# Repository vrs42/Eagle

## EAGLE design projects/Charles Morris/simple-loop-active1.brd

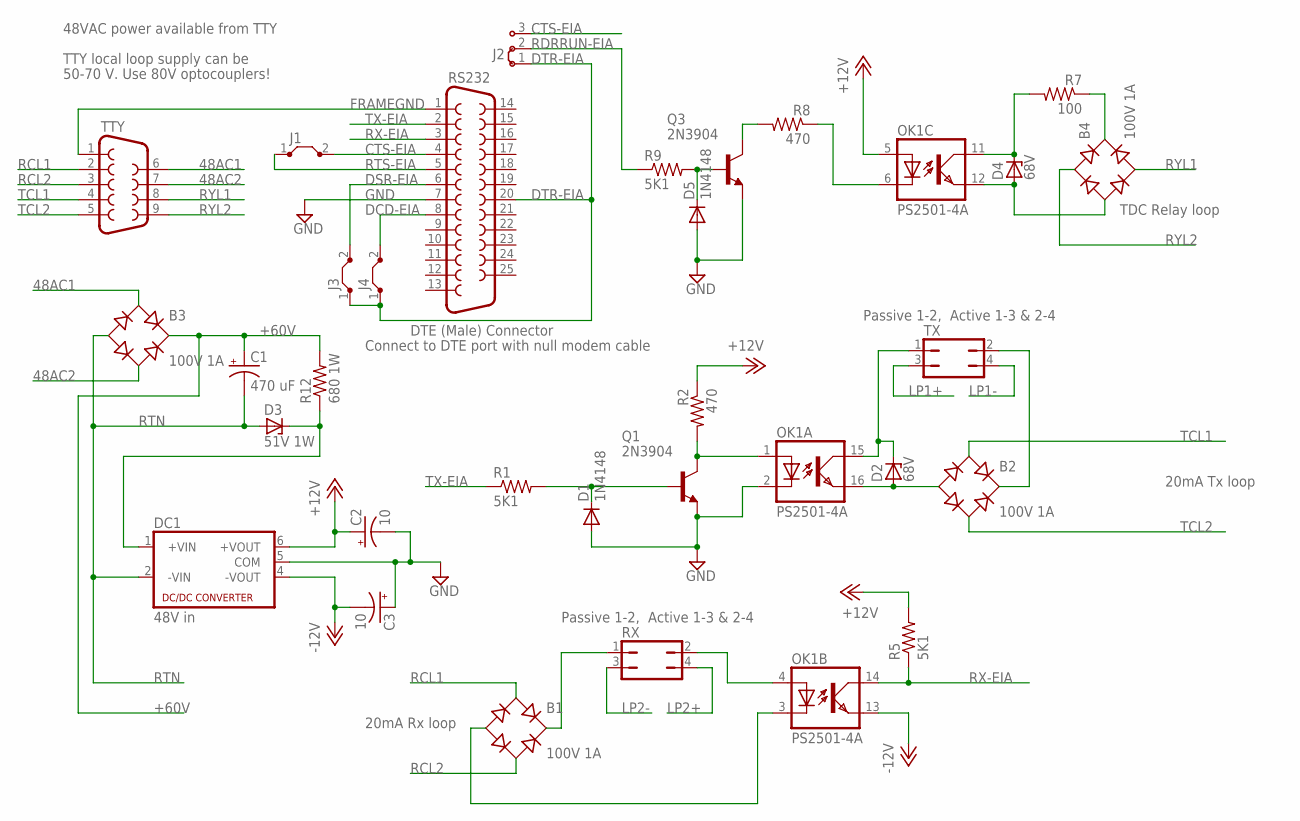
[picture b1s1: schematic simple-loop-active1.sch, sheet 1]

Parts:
B1, B2, B3, B4: 100V 1A; RB1A
C1: 470 uF; E7,5-18
C2, C3: 10; B45181A
D1, D5: 1N4148; DO35-10
D2, D4: 68V; DO41Z10
D3: 51V 1W; DO41Z10
DC1: 48V in; NMA
J1, J3, J4: J5MM; 05
J2: J2X5MM; 05C
OK1: PS2501-4A; DIL16
Q1, Q3: 2N3904; TO92
R1, R5, R9: 5K1; 0207/10
R2, R8: 470; 0207/10
R7: 100; 0207/10
R12: 680 1W; P0817V
RS232: F25H
RX: JP2Q
TTY: F09H
TX: JP2Q

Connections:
48AC1: B3.AC1, TTY.6
48AC2: B3.AC2, TTY.7
+12V: C2.+, DC1.6 (+VOUT), OK1.5 (A), R2.1, R5.2
+48VDC: D3.C, DC1.1 (+VIN), R12.1
+60V: B3.+, C1.+, R12.2; also elsewhere on the board
-12V: C3.-, DC1.4 (-VOUT), OK1.13 (EMIT)
CTS-EIA: J1.2, J2.3, RS232.4
DCD-EIA: J4.2, RS232.8
DSR-EIA: J3.2, RS232.6
DTR-EIA: J2.1, J3.1, J4.1, RS232.20
FRAMEGND: RS232.1, TTY.1
GND: C2.-, C3.+, D1.A, D5.A, DC1.5 (COM), OK1.2 (C), Q1.3 (E), Q3.3 (E), RS232.7
LP1+: TX.3; also elsewhere on the board
LP1-: TX.4; also elsewhere on the board
LP2+: RX.4; also elsewhere on the board
LP2-: RX.3; also elsewhere on the board
unnamed: OK1.4 (A), RX.2
unnamed: B1.+, RX.1
unnamed: B1.-, OK1.3 (C)
unnamed: B2.-, D2.A, OK1.16 (EMIT)
unnamed: D2.C, OK1.15 (COL), TX.1
unnamed: D1.C, Q1.2 (B), R1.2
unnamed: OK1.1 (A), Q1.1 (C), R2.2
unnamed: D4.C, OK1.11 (COL), R7.2
unnamed: B4.-, D4.A, OK1.12 (EMIT)
unnamed: B4.+, R7.1
unnamed: OK1.6 (C), R8.1
unnamed: D5.C, Q3.2 (B), R9.2
unnamed: Q3.1 (C), R8.2
unnamed: B2.+, TX.2
RCL1: B1.AC1, TTY.2
RCL2: B1.AC2, TTY.3
RDRRUN-EIA: J2.2, R9.1
RTN: B3.-, C1.-, D3.A, DC1.2 (-VIN); also elsewhere on the board
RTS-EIA: J1.1, RS232.5
RX-EIA: OK1.14 (COL), R5.1, RS232.3
RYL1: B4.AC2, TTY.8
RYL2: B4.AC1, TTY.9
TCL1: B2.AC1, TTY.4
TCL2: B2.AC2, TTY.5
TX-EIA: R1.1, RS232.2

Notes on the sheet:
DTE (Male) Connector
TTY local loop supply can be
50-70 V. Use 80V optocouplers!
20mA Tx loop
20mA Rx loop
48VAC power available from TTY
TDC Relay loop
Connect to DTE port with null modem cable
Passive 1-2, Active 1-3 & 2-4

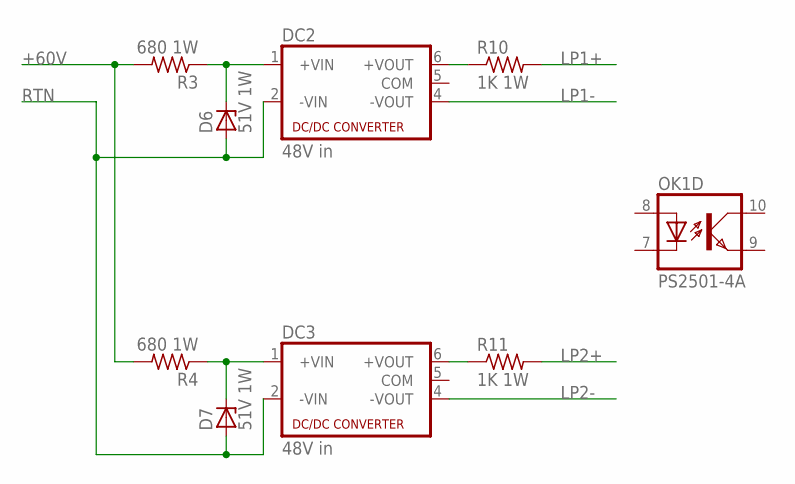
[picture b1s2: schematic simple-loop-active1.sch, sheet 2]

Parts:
D6, D7: 51V 1W; DO41Z10
DC2, DC3: 48V in; NMA
OK1: PS2501-4A; DIL16
R3, R4: 680 1W; P0817V
R10, R11: 1K 1W; P0817V

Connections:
+48VDC1: D6.C, DC2.1 (+VIN), R3.1
+48VDC2: D7.C, DC3.1 (+VIN), R4.1
+60V: R3.2, R4.2; also elsewhere on the board
LP1+: R10.2; also elsewhere on the board
LP1-: DC2.4 (-VOUT); also elsewhere on the board
LP2+: R11.2; also elsewhere on the board
LP2-: DC3.4 (-VOUT); also elsewhere on the board
unnamed: DC2.6 (+VOUT), R10.1
unnamed: DC3.6 (+VOUT), R11.1
RTN: D6.A, D7.A, DC2.2 (-VIN), DC3.2 (-VIN); also elsewhere on the board

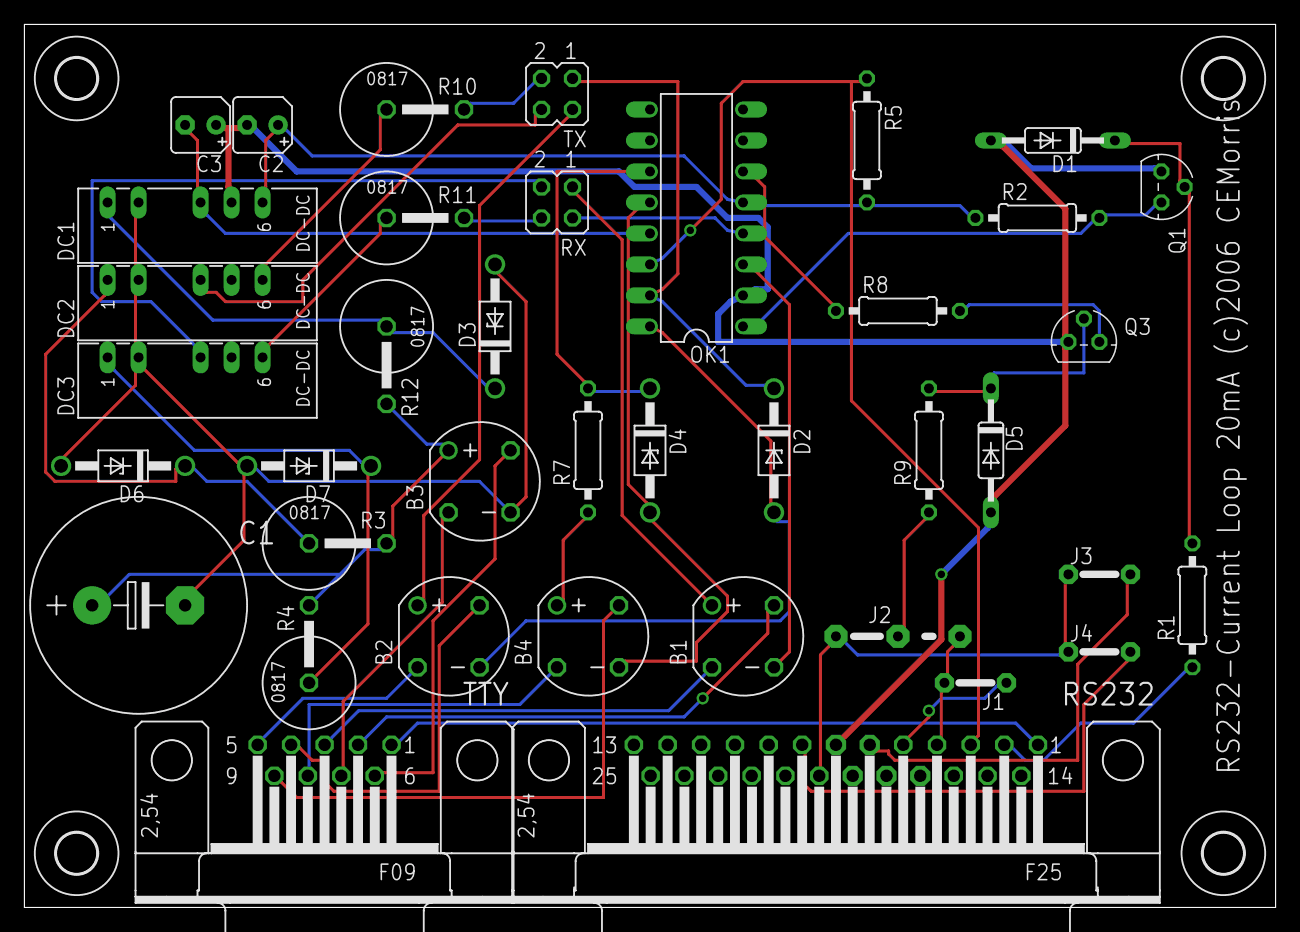
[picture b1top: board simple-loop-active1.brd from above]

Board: 2 copper layers, 102.5 x 72.4 mm, 43 parts (0 on the bottom side), 45 nets.

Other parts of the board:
U$1, U$2, U$3, U$4: 3,3

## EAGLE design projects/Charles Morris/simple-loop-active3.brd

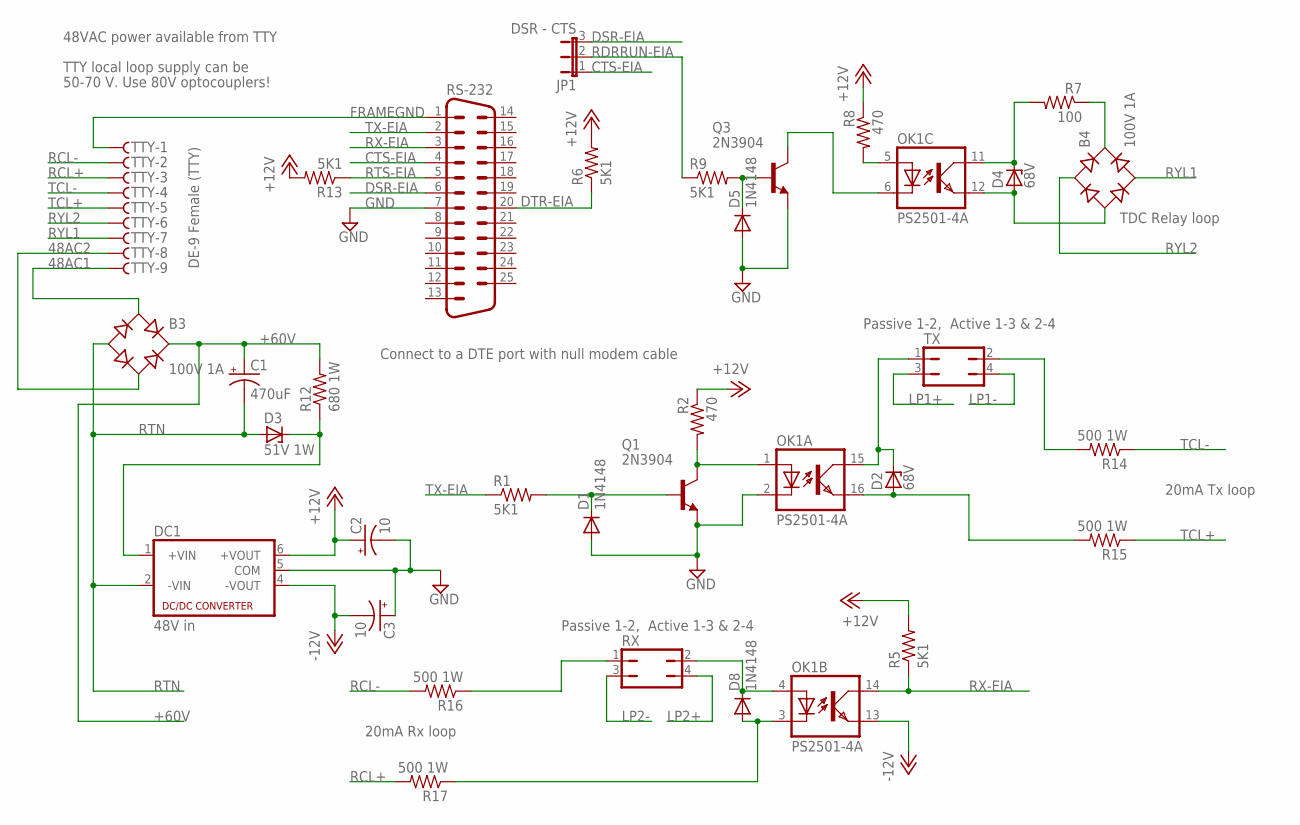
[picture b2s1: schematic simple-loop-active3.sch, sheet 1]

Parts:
B3, B4: 100V 1A; RB1A
C1: 470uF; E7,5-18
C2, C3: 10; B45181A
D1, D5, D8: 1N4148; DO35-10
D2, D4: 68V; DO41Z10
D3: 51V 1W; DO41Z10
DC1: 48V in; NMA
JP1: DSR - CTS; JP2
OK1: PS2501-4A; DIL16
Q1, Q3: 2N3904; TO92
R1, R5, R6, R9, R13: 5K1; 0207/10
R2, R8: 470; 0207/10
R7: 100; 0207/10
R12: 680 1W; P0817V
R14, R15, R16, R17: 500 1W; P0817V
RS-232: M25H
RX: JP2Q
TTY: F09HS; F09H
TX: JP2Q

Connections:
48AC1: B3.AC1, TTY.9
48AC2: B3.AC2, TTY.8
+12V: C2.+, DC1.6 (+VOUT), R2.1, R5.2, R6.2, R8.1, R13.2
+48VDC: D3.C, DC1.1 (+VIN), R12.1
+60V: B3.+, C1.+, R12.2; also elsewhere on the board
-12V: C3.-, DC1.4 (-VOUT), OK1.13 (EMIT)
CTS-EIA: JP1.1, RS-232.4
DSR-EIA: JP1.3, RS-232.6
DTR-EIA: R6.1, RS-232.20
FRAMEGND: RS-232.1, TTY.1
GND: C2.-, C3.+, D1.A, D5.A, DC1.5 (COM), OK1.2 (C), Q1.3 (E), Q3.3 (E), RS-232.7
LP1+: TX.3; also elsewhere on the board
LP1-: TX.4; also elsewhere on the board
LP2+: RX.4; also elsewhere on the board
LP2-: RX.3; also elsewhere on the board
unnamed: D8.C, OK1.4 (A), RX.2
unnamed: R16.1, RX.1
unnamed: D8.A, OK1.3 (C), R17.1
unnamed: D2.A, OK1.16 (EMIT), R15.2
unnamed: OK1.5 (A), R8.2
unnamed: D2.C, OK1.15 (COL), TX.1
unnamed: D1.C, Q1.2 (B), R1.2
unnamed: OK1.1 (A), Q1.1 (C), R2.2
unnamed: D4.C, OK1.11 (COL), R7.2
unnamed: B4.-, D4.A, OK1.12 (EMIT)
unnamed: B4.+, R7.1
unnamed: OK1.6 (C), Q3.1 (C)
unnamed: D5.C, Q3.2 (B), R9.2
unnamed: R14.2, TX.2
RCL+: R17.2, TTY.3
RCL-: R16.2, TTY.2
RDRRUN-EIA: JP1.2, R9.1
RTN: B3.-, C1.-, D3.A, DC1.2 (-VIN); also elsewhere on the board
RTS-EIA: R13.1, RS-232.5
RX-EIA: OK1.14 (COL), R5.1, RS-232.3
RYL1: B4.AC2, TTY.7
RYL2: B4.AC1, TTY.6
TCL+: R15.1, TTY.5
TCL-: R14.1, TTY.4
TX-EIA: R1.1, RS-232.2

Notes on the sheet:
TTY local loop supply can be
50-70 V. Use 80V optocouplers!
20mA Tx loop
20mA Rx loop
48VAC power available from TTY
TDC Relay loop
Connect to a DTE port with null modem cable
Passive 1-2, Active 1-3 & 2-4
DE-9 Female (TTY)

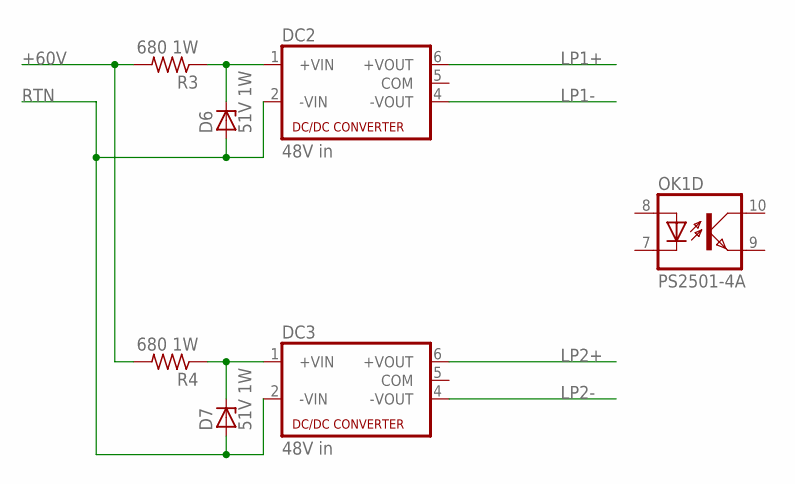
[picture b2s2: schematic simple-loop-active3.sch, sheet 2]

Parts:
D6, D7: 51V 1W; DO41Z10
DC2, DC3: 48V in; NMA
OK1: PS2501-4A; DIL16
R3, R4: 680 1W; P0817V

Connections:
+48VDC1: D6.C, DC2.1 (+VIN), R3.1
+48VDC2: D7.C, DC3.1 (+VIN), R4.1
+60V: R3.2, R4.2; also elsewhere on the board
LP1+: DC2.6 (+VOUT); also elsewhere on the board
LP1-: DC2.4 (-VOUT); also elsewhere on the board
LP2+: DC3.6 (+VOUT); also elsewhere on the board
LP2-: DC3.4 (-VOUT); also elsewhere on the board
RTN: D6.A, D7.A, DC2.2 (-VIN), DC3.2 (-VIN); also elsewhere on the board

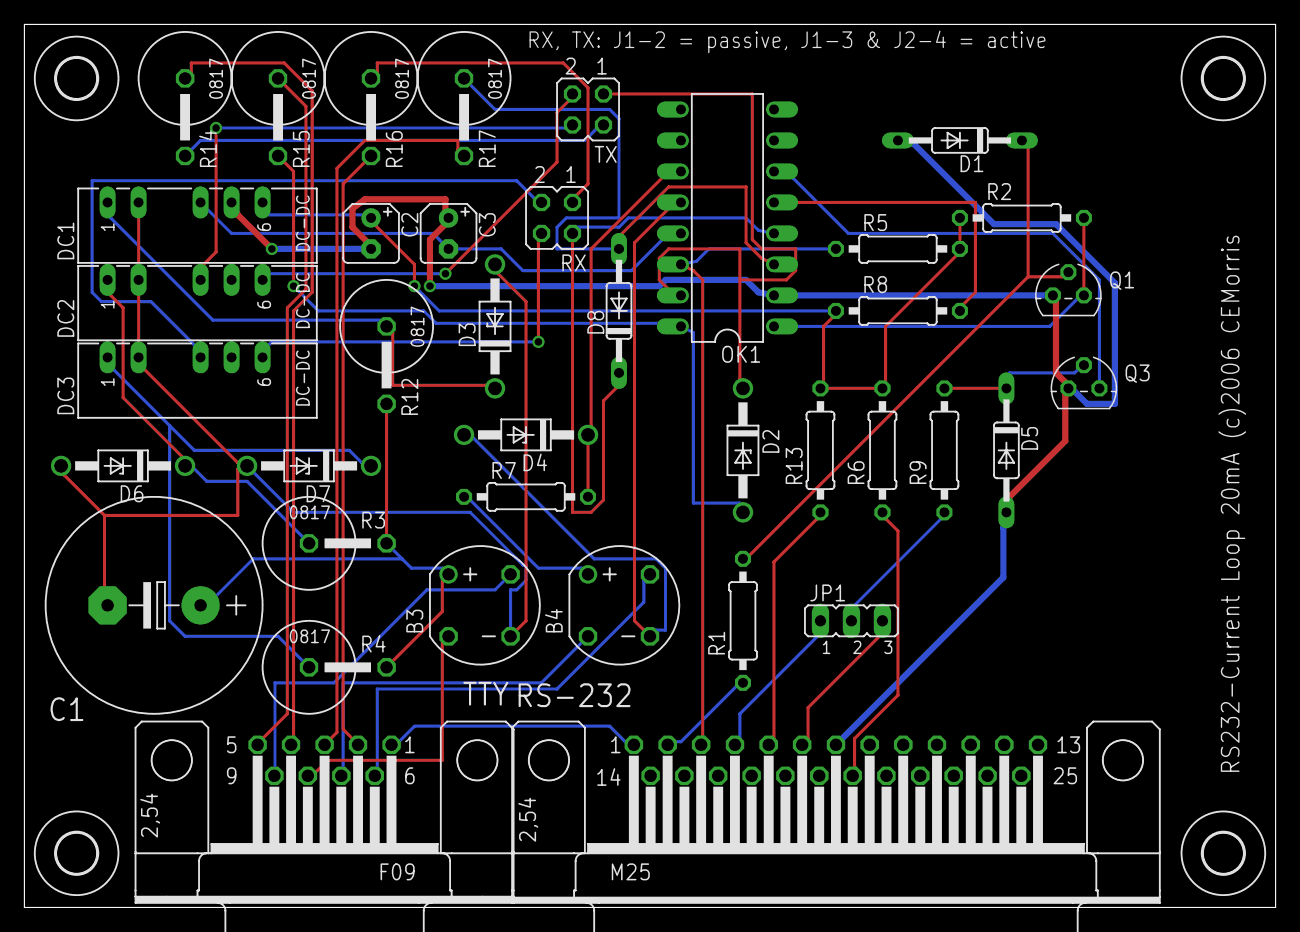
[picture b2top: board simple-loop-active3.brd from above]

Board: 2 copper layers, 102.5 x 72.4 mm, 43 parts (0 on the bottom side), 42 nets.

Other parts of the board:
U$1, U$2, U$3, U$4: 3,3

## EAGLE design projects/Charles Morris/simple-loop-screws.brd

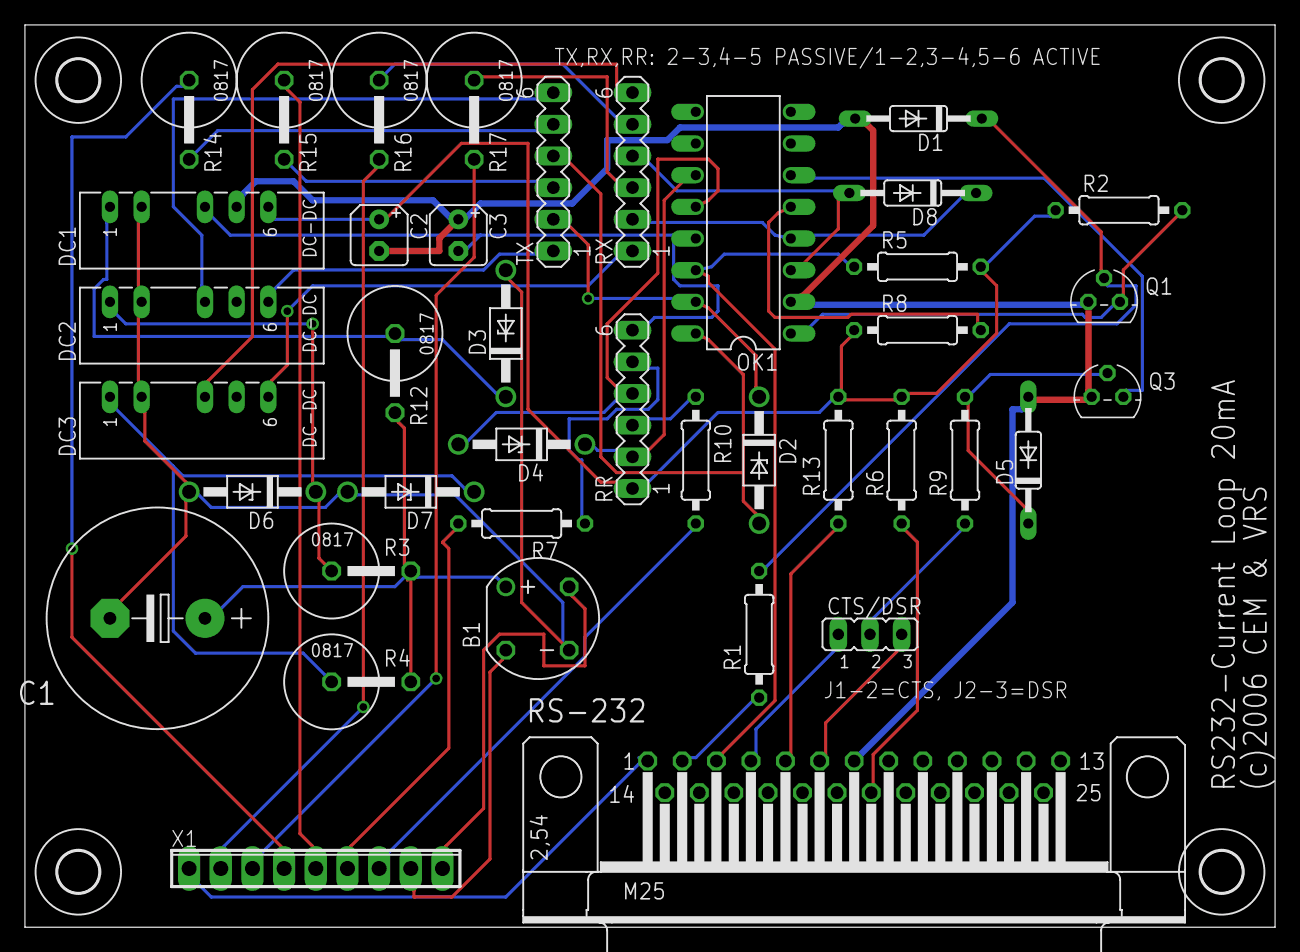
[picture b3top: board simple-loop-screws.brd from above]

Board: 2 copper layers, 100.3 x 72.4 mm, 44 parts (0 on the bottom side), 45 nets.

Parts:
B1: 100V 1A; RB1A
C1: 470 uF; E7,5-18
C2, C3: 10; B45181A
CTS/DSR: JP2
D1, D5, D8: 1N4148; DO35-10
D2, D4: 68V; DO41Z10
D3, D6, D7: 51V 1W; DO41Z10
DC1: RS232/RdrRun; NMA
DC2: TX LOOP; NMA
DC3: RX LOOP; NMA
OK1: PS2501-4A; DIL16
Q1, Q3: 2N3904; TO92
R1, R5, R6, R9, R13: 5K1; 0207/10
R2, R7, R8, R10: 430; 0207/10
R3, R4, R12: 680 1W; P0817V
R14, R15, R16, R17: 510 1W; P0817V
RR: MA06-1
RS-232: M25H
RX: MA06-1
TX: MA06-1
U$1, U$2, U$3, U$4: 3,3
X1: FG -RX+ -TX+ -RY+ 48AC; 9POL254

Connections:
48AC1: B1.AC1, X1.9
48AC2: B1.AC2, X1.8
+12V: C2.+, DC1.6, R2.1, R5.2, R6.2, R8.1, R13.2, RR.1
+48VDC: D3.C, DC1.1, R12.1
+48VDC1: D6.C, DC2.1, R3.1
+48VDC2: D7.C, DC3.1, R4.1
+60V: B1.+, C1.+, R3.2, R4.2, R12.2
-12V: C3.-, DC1.4, OK1.13, RR.6
CTS-EIA: CTS/DSR.1, RS-232.4
DSR-EIA: CTS/DSR.3, RS-232.6
DTR-EIA: R6.1, RS-232.20
FRAMEGND: RS-232.1, X1.1
GND: C2.-, C3.+, D1.A, D5.A, DC1.5, OK1.2, Q1.3, Q3.3, RS-232.7
LP1+: DC2.6, TX.1
LP1-: DC2.4, TX.6
LP2+: DC3.6, RX.1
LP2-: DC3.4, RX.6
unnamed: D8.C, OK1.4, RX.2
unnamed: R16.1, RX.5
unnamed: D8.A, OK1.3, RX.4
unnamed: D2.A, OK1.16, TX.4
unnamed: OK1.5, R8.2
unnamed: D2.C, OK1.15, TX.2
unnamed: D1.C, Q1.2, R1.2
unnamed: D4.C, OK1.11, RR.2
unnamed: OK1.1, Q1.1, R2.2
unnamed: R10.1, RR.3
unnamed: R7.1, RR.5
unnamed: OK1.6, Q3.1
unnamed: D5.C, Q3.2, R9.2
unnamed: R14.2, TX.5
unnamed: R17.1, RX.3
unnamed: R15.2, TX.3
unnamed: D4.A, OK1.12, RR.4
RCL+: R17.2, X1.3
RCL-: R16.2, X1.2
RDRRUN-EIA: CTS/DSR.2, R9.1
RTN: B1.-, C1.-, D3.A, D6.A, D7.A, DC1.2, DC2.2, DC3.2
RTS-EIA: R13.1, RS-232.5
RX-EIA: OK1.14, R5.1, RS-232.3
RYL+: R10.2, X1.7
RYL-: R7.2, X1.6
TCL+: R15.1, X1.5
TCL-: R14.1, X1.4
TX-EIA: R1.1, RS-232.2

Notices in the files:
projects/Charles Morris/simple-loop-active1.brd:
RS232-Current Loop 20mA (c)2006 CEMorris
projects/Charles Morris/simple-loop-screws.brd:
(c)2006 CEM & VRS
